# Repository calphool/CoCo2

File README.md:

# CoCo2

## February 8, 2020

This is my collection area for Tandy Color Computer 2 Projects.  I've only got one at the moment.  It's a composite video mod for the CoCo 2.  The CoCo was designed 
in a time when it was perfectly reasonable to assume that all televisions had an analog RF input.  Of course that's no longer the case, so something has to be done 
to get a CoCo 2 to work on a modern monitor or television.  

My CoCo 2 has a [vertically oriented RF modulator](./motherboard.jpeg).  So, I designed a replacement PCB for the inside of the RF modulator to convert it to a 
composite out and sound out RCA port.  I desoldered the MC1372 chip from inside the old modulator board, since I'm repurposing that chip.

I'm not an expert, but it appears that the video graphics display chip of the CoCo2 (the MC6847) outputs a luminance and two chrominance channels (called PHI-A and PHI-B).
Even though one of these is a luminance channel, and in theory could drive a black and white composite signal, it isn't at the right voltage levels or bias, and so it 
must both be conditioned and mixed with the chrominance channels.  That's where the MC1372 chip comes in.  Originally intended as an RF signal generator, it has a 
useful "test mode" that allows it to output a mixed composite (or CVBS) signal that can then be conditioned to drive a television monitor that accepts CVBS, which most 
TVs still accept (though some very modern ones don't have separate inputs for it -- they accept the CVBS channel on the green RGB input).

Basically the way you accomplish this is to put a diode between pins 13 and 14 of the MC1372, which is where the "tank" circuit is supposed to go, which traditionally 
was used to "tune" the output to match the expected frequency rate for analog channel 3 or 4 on a traditional television.  With the tank circuit bipassed, the chip 
produces a plain composite signal with colors mixed in appropriately.  So, then you simply use some transistors to get the signal into the right level and bias, and tune the 
bias level with a potentiometer.  I also included a potentiometer to tune the output level of the sound signal.  

With some right angle headers, you can simply plug this board in where the original RF modulator can went.  I made the PCB the same size as the original PCB in the 
RF can, so hopefully I'll be able to put it back in the can, drill another hole for the sound RCA jack, drill a clean hole in the back of the CoCo 2 case right where the 
"channel select" hole was, and it should be a nice clean little mod.

As an FYI, there also exists a [VGA mod](http://www.cocovga.com/) that can be purchased for the CoCo 2, which uses a FPGA and plugs right into the socket where the video display generator chip 
(the MC6847) sits.  This would probably be the cleanest signal you can get out of a CoCo 2.

I may decide to build my own VGA or HDMI board, though if I do, I may use the outputs of the original MC6847 rather than "co-opting" it like the the CoCoVGA does.  I've 
wanted to learn how to program FPGAs, and I found this [little reference](http://ocw.abu.edu.ng/courses/electrical-engineering-and-computer-science/6-111-introductory-digital-systems-laboratory-fall-2002/lecture-notes/l18.pdf) to an approach for how to coax a digital signal out of the analog outputs of the MC6847.
Using that approach, I think it would be possible to use the [AM26LS32](http://www.ti.com/lit/ds/symlink/am26ls32ac.pdf) to feed a FPGA (probably along with a few other 
signals from the MC6847 to be able to detect sync signals) to paint an in-memory video buffer, and then figure out some way to push that buffer out an HDMI (TMDS) port.  

I've attached a few pictures below to help someone who was building one of these.

The first picture shows the view from behind.    Notice that I used a Y cable for the RCA jacks, one for 
composite video and the other for audio.  They share a common ground.  You could just wire your cable directly to the PCB if you were okay with having 
cables hanging out of the back of the machine (which wouldn't be a huge issue, since the CoCo actually has a power cable permanently attached).

The second picture shows how the Y cable is connected. .

The third shows a front-on view.   There are a couple of things to notice.  First, you can see the right angle 
header connecting the Coco's motherboard to the composite board, and also a wire going from ground on the composite board to a hole where the original can was soldered (it's grounded on the 
motherboard).  The next thing to notice is at the top.  R1 and D1 are not installed as the 1.0 PCB shows.  I made a mistake on the original schematic.  So, 
what you can see here is that D1 is inserted in the opposite direction of what the PCB shows (the orientation band is to the RIGHT, not the LEFT).  Also, 
you can see a hacky pair of resistors soldered together.  I didn't have a 360 ohm resistor, so I "made one" by combining a 330 ohm and a 39 ohm, which was 
close enough.  If you have a 360 ohm, you can make a cleaner hack.  Notice that the resistor pair is inserted in the TOP hole for R1, and R1's bottom hole 
is left empty, and the other end of the resistor pair is soldered to the back of D1.

The fourth shows a close up view.  

The fifth shows another top view  where you can clearly see that D1 is in the opposite orientation of what shows 
on the PCB. It's pretty important that if you decide to build this PCB, you follow the PDF instructions carefully.

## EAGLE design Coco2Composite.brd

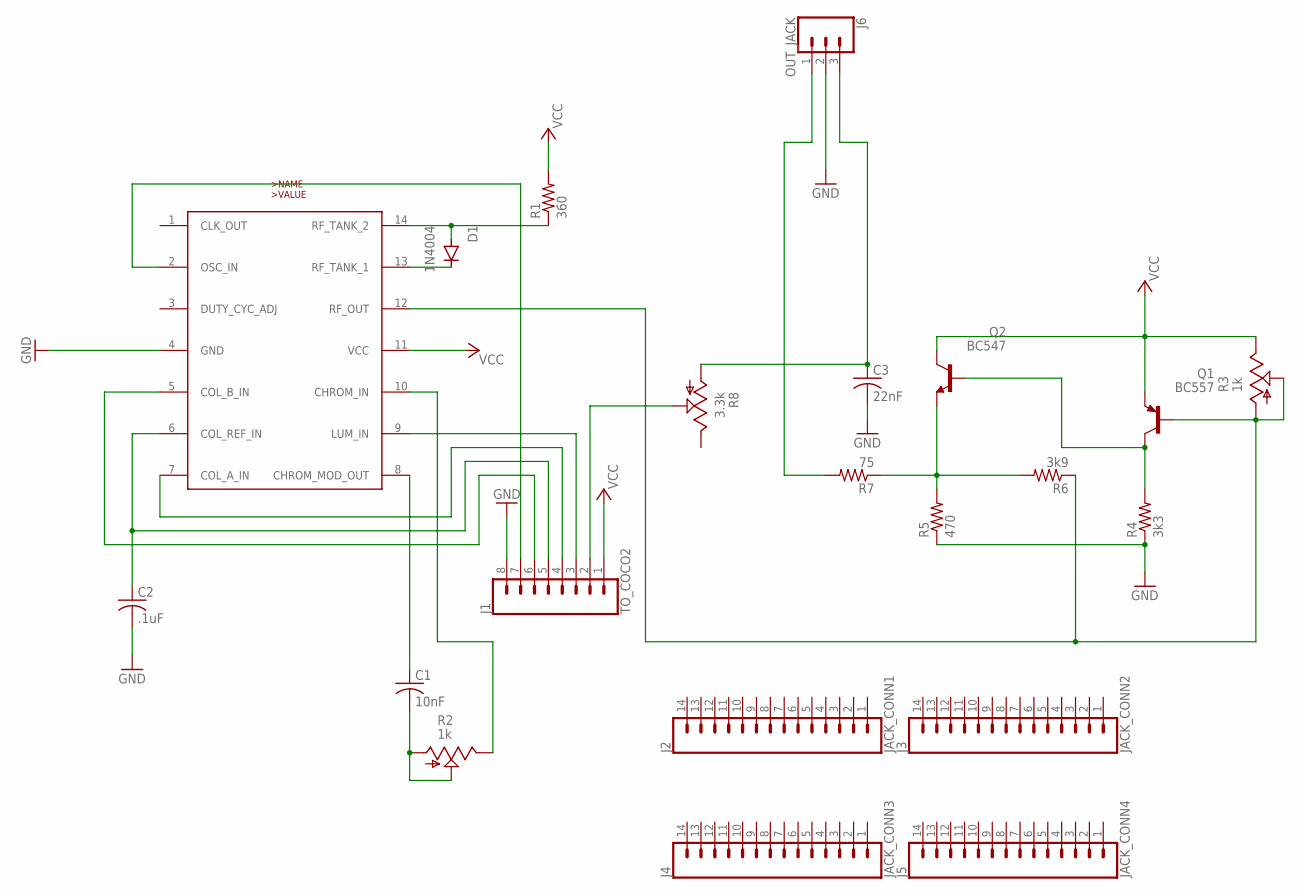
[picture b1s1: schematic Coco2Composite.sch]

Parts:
C1: 10nF; C025-024X044
C2: .1uF; C025-024X044
C3: 22nF; C025-024X044
D1: 1N4004; DO41-10
J1: TO_COCO2; 1X08
J2: JACK_CONN1; 1X14
J3: JACK_CONN2; 1X14
J4: JACK_CONN3; 1X14
J5: JACK_CONN4; 1X14
J6: OUT_JACK; 1X03
Q1: BC557; TO92-EBC
Q2: BC547; TO92
R1: 360; 0204V
R2, R3: 1k; B25U
R4: 3k3; 0204V
R5: 470; 0204V
R6: 3k9; 0204V
R7: 75; 0204V
R8: 3.3k; B25U
U1: MC1372; DIP14

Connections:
CHB: C2.1, J1.5, U1.6 (COL_REF_IN)
CLK: J1.7, U1.2 (OSC_IN)
GND: C2.2, C3.2, J1.8, J6.2, R4.1, R5.1, U1.4 (GND)
unnamed: D1.C, U1.13 (RF_TANK_1)
unnamed: D1.A, R1.1, U1.14 (RF_TANK_2)
unnamed: C1.1, U1.8 (CHROM_MOD_OUT)
unnamed: C1.2, R2.A, R2.S
unnamed: R2.E, U1.10 (CHROM_IN)
unnamed: Q1.B, R3.A, R3.S, R6.1, U1.12 (RF_OUT)
unnamed: Q1.C, Q2.2 (B), R4.2
unnamed: Q2.1 (E), R5.2, R6.2, R7.1
unnamed: J6.1, R7.2
unnamed: C3.1, J6.3, R8.A
PHIB: J1.6, U1.5 (COL_B_IN)
PHI_A: J1.4, U1.7 (COL_A_IN)
SND: J1.2, R8.S
VCC: J1.1, Q1.E, Q2.3 (C), R1.2, R3.E, U1.11 (VCC)
Y: J1.3, U1.9 (LUM_IN)

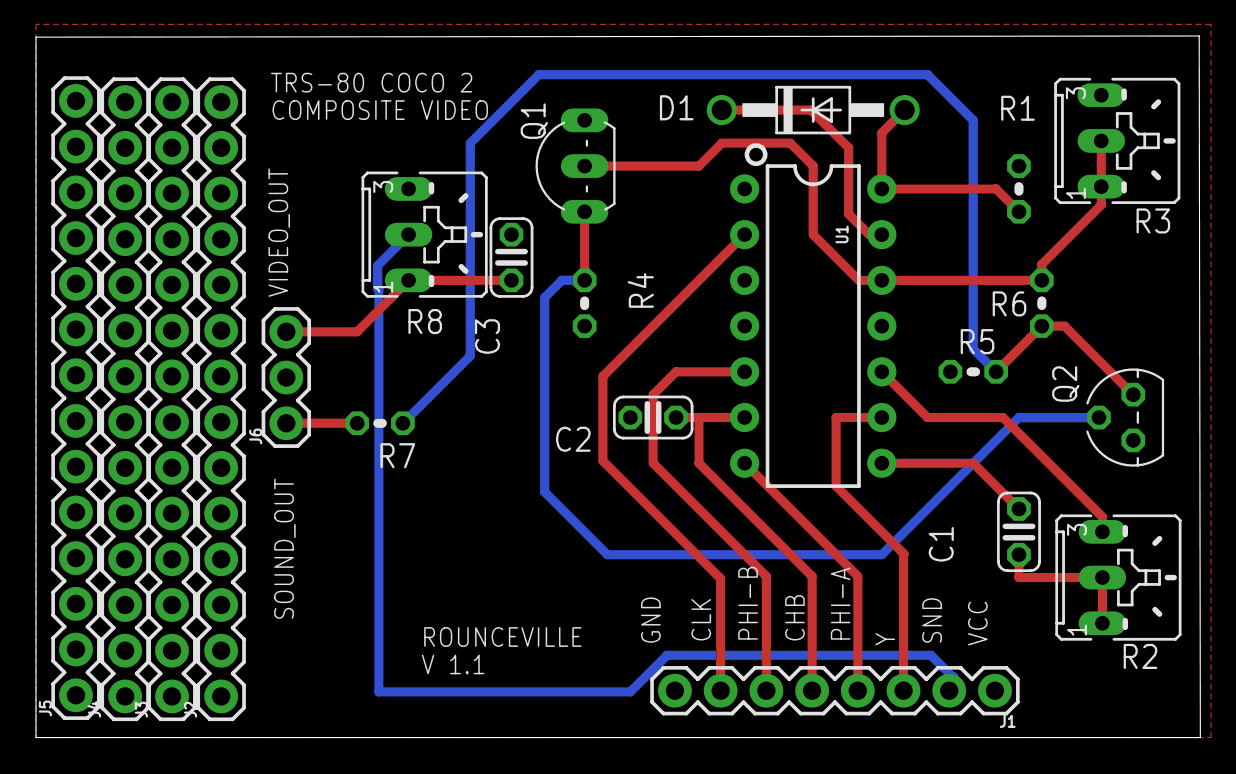
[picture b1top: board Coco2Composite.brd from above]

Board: 2 copper layers, 64.7 x 39.0 mm, 21 parts (0 on the bottom side), 18 nets.

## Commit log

2020-02-09 CoCo2 Composite Video / Audio PCB Design
2020-02-09 pdfs of board and schematic
2020-02-27 v1.1 revision
2020-02-28 added instructions
2025-05-18 added some photos
2025-05-18 fixed typo
2025-05-18 fixed type

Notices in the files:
parts and their libraries:
SparkFun-Connectors: Licensing: Creative Commons ShareAlike 4.0 International - https://creativecommons.org/licenses/by-sa/4.0
